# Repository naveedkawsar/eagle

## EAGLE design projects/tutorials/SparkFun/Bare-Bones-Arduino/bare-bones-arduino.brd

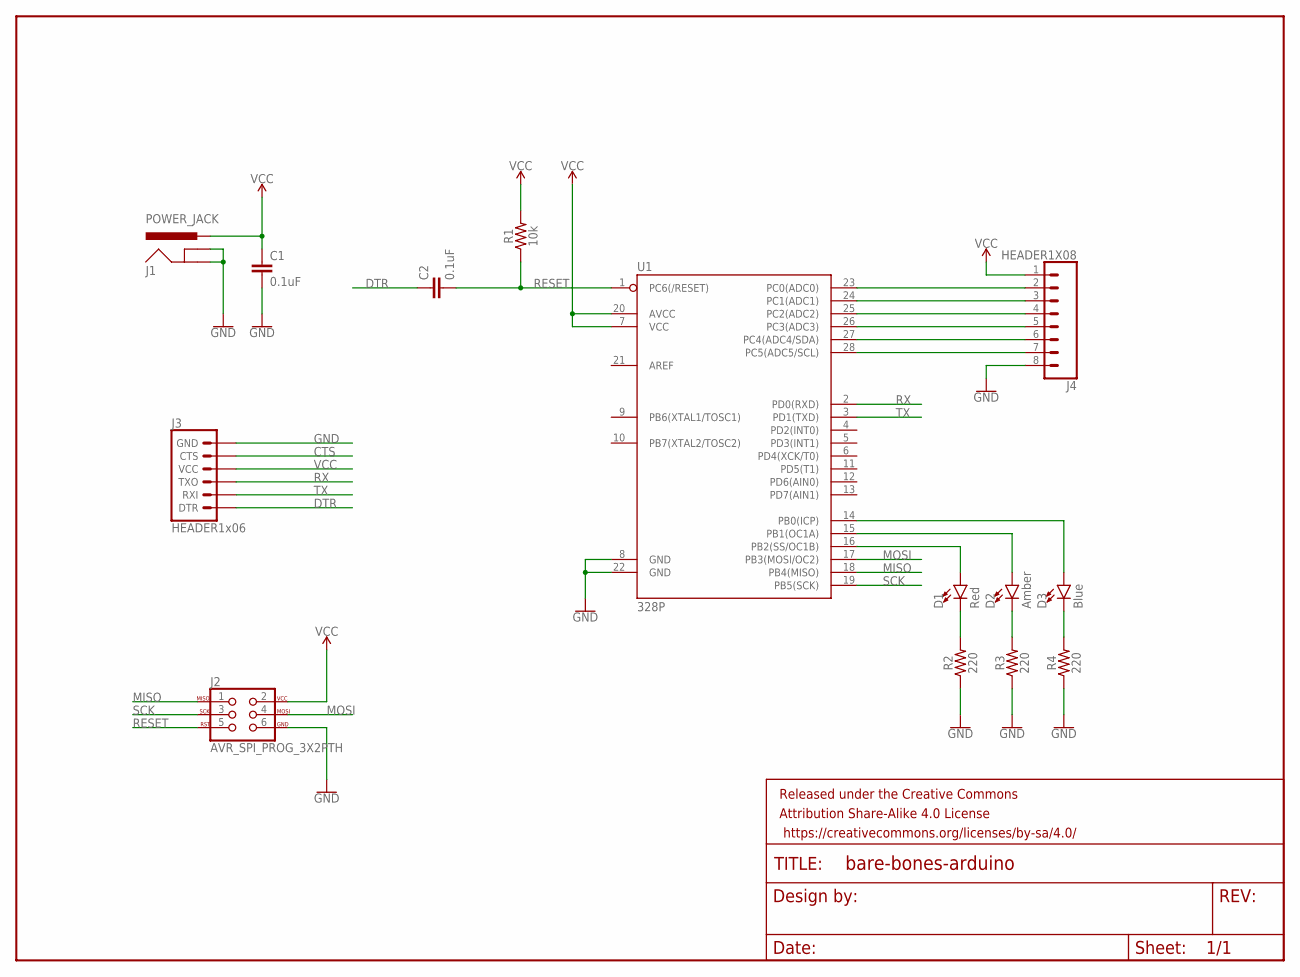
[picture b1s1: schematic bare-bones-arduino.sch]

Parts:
C1, C2: 0.1uF; CAP-PTH-SMALL-KIT
D1: Red; LED_5MM
D2: Amber; LED_5MM
D3: Blue; LED_5MM
FRAME1: FRAME-LETTERNO_PACKAGE; DUMMY
J1: POWER_JACK; POWER_JACK_PTH
J2: AVR_SPI_PROG_3X2PTH; 2X3
J3: HEADER1x06; 1X06
J4: HEADER1X08; 1X08
R1: 10k; AXIAL-0.3
R2, R3, R4: 220; AXIAL-0.3
U1: 328P; DIP28

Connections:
CTS: J3.5 (CTS)
DTR: C2.1, J3.1 (DTR)
GND: C1.2, J1.GND, J1.GNDBREAK, J2.6, J3.6 (GND), J4.8, R2.P$1 (1), R3.P$1 (1), R4.P$1 (1), U1.8 (GND), U1.22 (GND)
MISO: J2.1, U1.18 (PB4(MISO))
MOSI: J2.4, U1.17 (PB3(MOSI/OC2))
unnamed: D1.A, U1.16 (PB2(SS/OC1B))
unnamed: D1.K (C), R2.P$2 (2)
unnamed: D2.K (C), R3.P$2 (2)
unnamed: D2.A, U1.15 (PB1(OC1A))
unnamed: D3.K (C), R4.P$2 (2)
unnamed: D3.A, U1.14 (PB0(ICP))
unnamed: J4.2, U1.23 (PC0(ADC0))
unnamed: J4.3, U1.24 (PC1(ADC1))
unnamed: J4.4, U1.25 (PC2(ADC2))
unnamed: J4.5, U1.26 (PC3(ADC3))
unnamed: J4.6, U1.27 (PC4(ADC4/SDA))
unnamed: J4.7, U1.28 (PC5(ADC5/SCL))
RESET: C2.2, J2.5, R1.P$1 (1), U1.1 (PC6(/RESET))
RX: J3.3 (TXO), U1.2 (PD0(RXD))
SCK: J2.3, U1.19 (PB5(SCK))
TX: J3.2 (RXI), U1.3 (PD1(TXD))
VCC: C1.1, J1.PWR, J2.2, J3.4 (VCC), J4.1, R1.P$2 (2), U1.7 (VCC), U1.20 (AVCC)

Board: 2 copper layers, 15 parts (0 on the bottom side), 21 nets, no tracks yet.

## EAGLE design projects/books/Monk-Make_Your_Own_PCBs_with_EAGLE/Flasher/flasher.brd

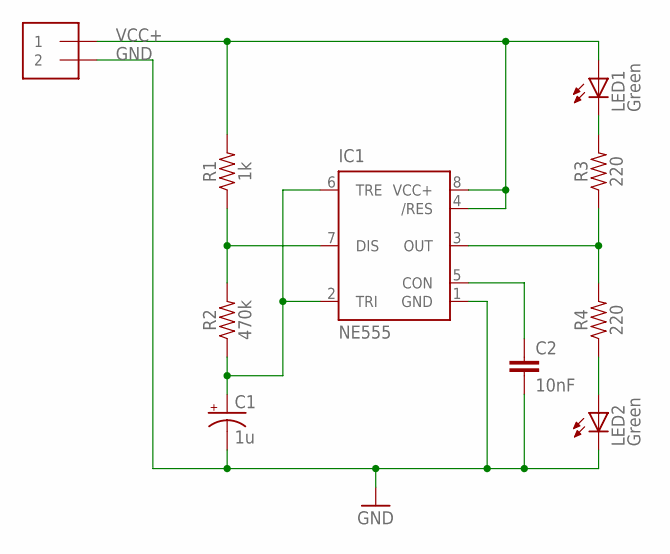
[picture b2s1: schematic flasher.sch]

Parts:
C1: 1u; E2,5-5
C2: 10nF; CAP-PTH-10MM
IC1: NE555; DIL-08
J1: 1X2-3.5MM
LED1, LED2: Green; LED5MM
R1: 1k; AXIAL-0.3
R2: 470k; AXIAL-0.3
R3, R4: 220; 0603

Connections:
GND: C1.-, C2.2, IC1.1 (GND), J1.2, LED2.K (C)
unnamed: LED1.K (C), R3.2
unnamed: IC1.7 (DIS), R1.P$1 (1), R2.P$2 (2)
unnamed: IC1.3 (OUT), R3.1, R4.2
unnamed: C1.+, IC1.2 (TRI), IC1.6 (TRE), R2.P$1 (1)
unnamed: LED2.A, R4.1
unnamed: C2.1, IC1.5 (CON)
VCC+: IC1.4 (/RES), IC1.8 (VCC+), J1.1, LED1.A, R1.P$2 (2)

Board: 2 copper layers, 10 parts (0 on the bottom side), 8 nets, no tracks yet.

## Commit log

2017-09-11 Initial commit of Eagle setup with SparkFun, Adafruit, Autodesk community libraries and script(s)
2017-09-11 Starting point of schematic capture for Flasher circuit with 555 timer and a Barebones Arduino
2017-09-11 First commit of 555-timer Flasher circuit board layout
2017-09-11 Updated flasher schematic
2017-09-11 Updated placement of components of flasher board layout
2017-09-12 Added values to headers to get rid of warnings
2017-09-12 Board and components imported from barebones Arduino schematic
2017-09-12 Updated barebones Arduino schematic with parts named
2017-09-19 First stab at component placement for barebones Arduino board

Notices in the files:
parts and their libraries:
SparkFun-Capacitors: Licensing: Creative Commons ShareAlike 4.0 International - https://creativecommons.org/licenses/by-sa/4.0
SparkFun-Aesthetics: Released under the Creative Commons Attribution Share-Alike 4.0 License
SparkFun-Aesthetics: https://creativecommons.org/licenses/by-sa/4.0
